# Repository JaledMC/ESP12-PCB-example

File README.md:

# ESP12-PCB-example
A PCB based on ESP12 to learn how to design boards with industry specifications in mind, using Kicad software. To learn more, go to:

* [Diseñando una PCB: Cómo no matarnos al primer intento](http://sialitech.com/electronica/disenando-pcb-como-no-matarnos/)
* [http://sialitech.com/electronica/programas-de-diseno-pcb-electronica/](http://sialitech.com/electronica/programas-de-diseno-pcb-electronica/)
* [Dividiendo la placa en módulos](http://sialitech.com/electronica/dividiendo-la-placa-en-modulos/)
* [¿Seleccionar los proveedores? ¡Si aún ni he cogido el lápiz!](http://sialitech.com/electronica/seleccionar-proveedor-pcb/)
* [Eligiendo a nuestro fabricante](http://sialitech.com/electronica/eligiendo-a-nuestro-fabricante-pcb/)
* [Esquema Eléctrico](http://sialitech.com/electronica/esquema-electrico-diseno-pcb/)
* [Diseño de la PCB I](http://sialitech.com/electronica/diseno-de-la-pcb-i/)

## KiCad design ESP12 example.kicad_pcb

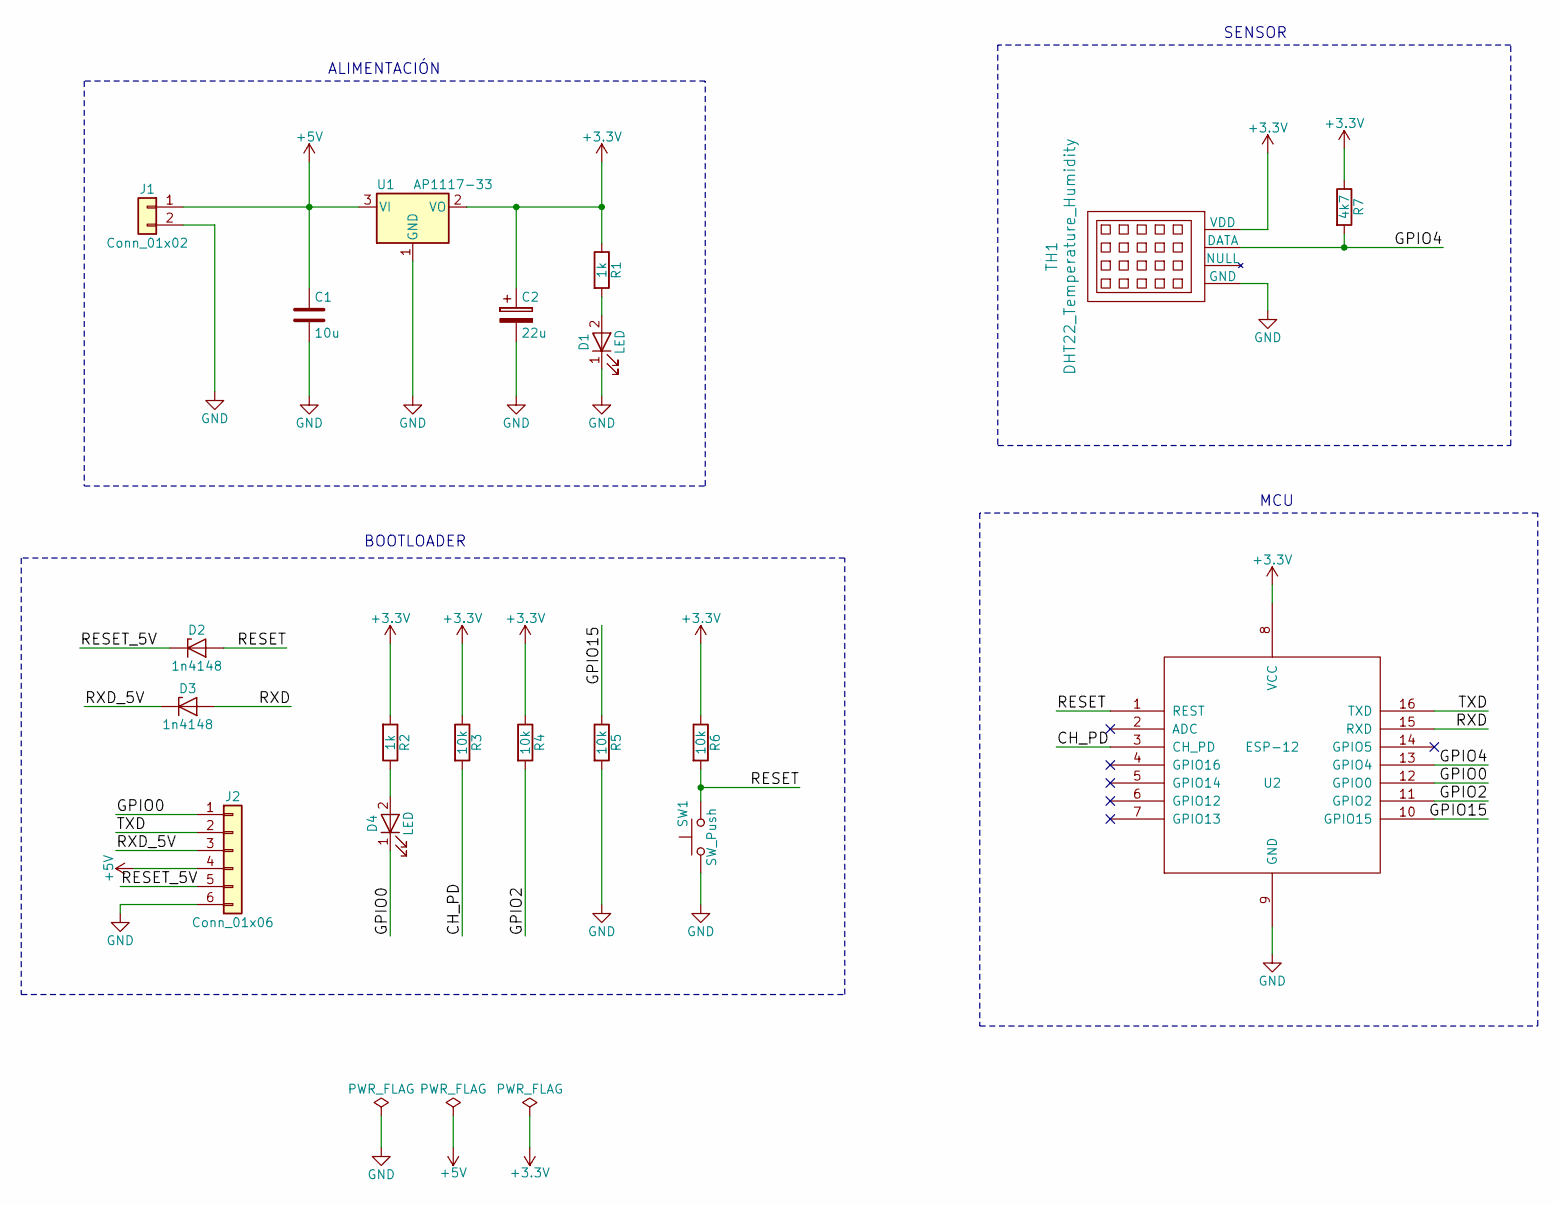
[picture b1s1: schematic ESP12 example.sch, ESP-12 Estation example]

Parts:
C1: 10u; C_1206
C2: 22u; CP_Elec_4x5.7
D1, D4: LED; LED_0805
D2, D3: 1n4148; D_SOD-123
J1: Conn_01x02; JST_EH_S02B-EH_02x2.50mm_Angled
J2: Conn_01x06; Pin_Header_Angled_1x06_Pitch2.54mm
R1, R2: 1k; R_1206
R3, R4, R5, R6: 10k; R_1206
R7: 4k7; Resistor_SMD+THTuniversal_1206_RM10_HandSoldering_RevA_Date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
SW1: SW_Push; SW_SPST_PTS645
TH1: DHT22_Temperature_Humidity
U1: AP1117-33; SOT-223-3Lead_TabPin2
U2: ESP-12

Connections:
+3V3: C2.1, R1.1, R2.2, R3.1, R4.1, R6.1, R7.1, TH1.1 (VDD), U1.2 (VO), U2.8 (VCC)
+5V: C1.1, J1.1, J2.4, U1.3 (VI)
/CH_PD: R3.2, U2.3 (CH_PD)
/GPIO0: D4.1 (K), J2.1, U2.12 (GPIO0)
/GPIO2: R4.2, U2.11 (GPIO2)
/GPIO4: R7.2, TH1.2 (DATA), U2.13 (GPIO4)
/GPIO15: R5.1, U2.10 (GPIO15)
/RESET: D2.2 (A), R6.2, SW1.2, U2.1 (REST)
/RESET_5V: D2.1 (K), J2.5
/RXD: D3.2 (A), U2.15 (RXD)
/RXD_5V: D3.1 (K), J2.3
/TXD: J2.2, U2.16 (TXD)
GND: C1.2, C2.2, D1.1 (K), J1.2, J2.6, R5.2, SW1.1, TH1.4 (GND), U1.1 (GND), U2.9 (GND)
unnamed: D1.2 (A), R1.2
unnamed: D4.2 (A), R2.1

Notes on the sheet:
ALIMENTACIÓN
BOOTLOADER
SENSOR
MCU

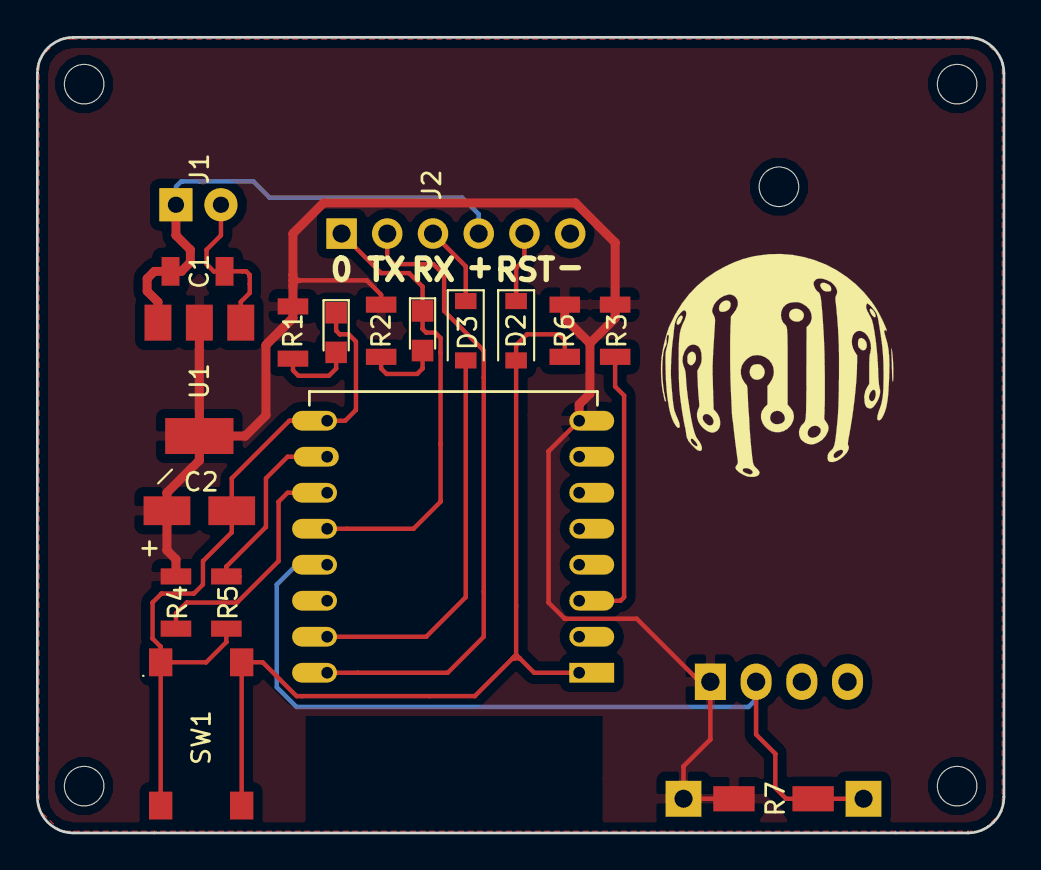
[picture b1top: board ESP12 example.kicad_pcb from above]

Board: 2 copper layers, 53.7 x 44.2 mm, 19 parts (0 on the bottom side), 15 nets.

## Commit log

2018-11-14 PCB design schematics
2018-11-14 Links
2018-11-15 Dumb fail
2019-01-03 Created using Colaboratory
